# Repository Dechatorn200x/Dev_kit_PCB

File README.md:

# 🚀 PCB Design Skill Development & Integration Portfolio

คลังเก็บรวบรวมโปรเจกต์การออกแบบแผงวงจรพิมพ์ (PCB Design) 
วัตถุประสงค์หลักเพื่อการศึกษา, พัฒนาทักษะ และทดลองใช้งานจริงในระบบฮาร์ดแวร์ โดยมุ่งเน้นการประยุกต์ใช้งานด้านอิเล็กทรอนิกส์กำลัง (Power Electronics), ระบบควบคุมอุตสาหกรรม (Industrial Automation) และการจัดการสัญญาณสัญญาณรบกวน (Signal Integrity) ผ่านโปรแกรม **KiCad**

---

## 🎯 เป้าหมายการพัฒนาทักษะ (Skill Development Goals)

* **Hardware Topology Learning:** ศึกษาและฝึกฝนการออกแบบวงจรลดแรงดันประสิทธิภาพสูง (Buck Converter), วงจรคัดแยกสัญญาณแบบ Optocoupler และโครงสร้างพอร์ตสื่อสารต่างๆ
* **PCB Layout Best Practices:** พัฒนาทักษะการจัดวางชิ้นส่วนอุปกรณ์ (Component Placement), การเดินลายเส้นทองแดงตามข้อกำหนดขนาดกระแสไฟฟ้า (Trace Width Constraints) และการจัดการระนาบกราวด์ (Ground Plane Area)
* **Design for Manufacturing (DFM):** ฝึกฝนการนำข้อมูลลายวงจรออกในรูปแบบเอกสารการผลิตจริง เช่น ไฟล์ Gerber, Drill files และตาราง BOM (Bill of Materials) เพื่อใช้เตรียมส่งโรงงานผลิต

---

## 📂 รายการโปรเจกต์บอร์ดทดสอบในคลัง (Project Sub-folders)

ตัวคลังแบ่งสัดส่วนโครงการออกเป็นโฟลเดอร์ย่อยตามฟังก์ชันและชิปประมวลผลหลัก เพื่อป้องกันความสับสนในการจัดการเวอร์ชัน:

### 📦 [01] Arduino Nano Integration Kit (`/01_Nano_Kit`)
บอร์ดทดสอบอเนกประสงค์เพื่อฝึกทักษะการวางระบบอินเตอร์เฟสพื้นฐานเข้ากับไมโครคอนโทรลเลอร์ **Arduino Nano**
* **ฟังก์ชันการเรียนรู้:** * ออกแบบระบบ Buck Converter (LM2596) แปลงระดับแรงดัน 12V เป็น 5V 
  * ออกแบบชุดพอร์ตสื่อสาร I2C และวงจร USB to TTL เพิ่มเติมสำหรับงาน Debug
  * ออกแบบบล็อก GPIO Isolated ขับโหลดมอเตอร์กระแสตรง 12V แยกกราวด์ป้องกันสัญญาณรบกวนย้อนกลับด้วย Optocoupler
  * ฝึกทักษะการสลับช่องสัญญาณ (Mode Selection Jumper) ยืดหยุ่นทิศทางสัญญาณพอร์ต I2C วิ่งกลับไปพอร์ตอะนาล็อกและดิจิทัลของบอร์ดควบคุม

### 📦 [02] Future Projects... (`/02_...`)
*(Please follow me.)*

---

## 🛠️ โปรแกรมและเครื่องมือหลักที่ใช้งาน (Toolchain)

* **EDA Software:** KiCad Suite (เวอร์ชัน 9.0 หรือล่าสุด) สำหรับวาดผัง Schematic วาดลายเส้น PCB ลายทองแดง และจำลองโมเดลชิ้นส่วนแบบ 3 มิติ
* **Version Control:** Git & GitHub สำหรับเก็บบันทึกประวัติเวอร์ชันของบอร์ด และจัดการไฟล์แบ็กอัปขยะอย่างเป็นระบบด้วย `.gitignore`

---

## 📝 บันทึกความก้าวหน้าและการพัฒนา (Development Log)
* **[2026-06]:** จัดโครงสร้างคลังเก็บงานใหม่เข้าสู่ระบบ Sub-folders, ออกแบบและทดสอบผังวงจร Schematic ของบอร์ดทดลองแรก (Arduino Nano Integration Kit) สำเร็จลุล่วงเป็นระบบเปิด

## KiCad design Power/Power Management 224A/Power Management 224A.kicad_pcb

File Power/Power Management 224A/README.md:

# ⚡ Power Supply USB 5V-28V (Model: 224A)

โปรเจกต์บอร์ดจ่ายไฟอเนกประสงค์ควบคุมด้วยไอซี (IC-Based Adjustable Power Supply) รองรับการอินพุตพลังงานผ่านพอร์ต USB และสามารถปรับแรงดันเอาต์พุตได้ยืดหยุ่นตั้งแต่ **5V ถึง 28V** ออกแบบด้วยโปรแกรม KiCad เหมาะสำหรับนำไปใช้เป็นชุดทดสอบวงจร (Development Kit) บอร์ดขยายกำลัง หรือระบบจัดการพลังงานในงานอิเล็กทรอนิกส์

---

## 🛠️ คุณสมบัติทางเทคนิค (Features)
* **Input Voltage:** รองรับการจ่ายไฟเข้าผ่านพอร์ต USB (`V_USB`) และพอร์ต Screw Terminal
* **Output Voltage Range:** สามารถปรับแรงดันเอาต์พุตได้กว้างตั้งแต่ **5V ถึง 28V**
* **Safety & Protections:** * มีระบบป้องกันสัญญาณรบกวนและการไหลย้อนกลับของกระแสไฟฟ้า
  * ไฟแสดงสถานะความผิดพลาด (Error LED) สำหรับแจ้งเตือนระบบ
* **PCB Design:** ออกแบบบอร์ดแบบ 4 เลเยอร์ (4 layers Copper) พร้อมการจัดสัดส่วนลายทองแดงสำหรับไลน์กำลัง (Power Plane) และกราวด์ (GND Plane) ที่หนาแน่น

---

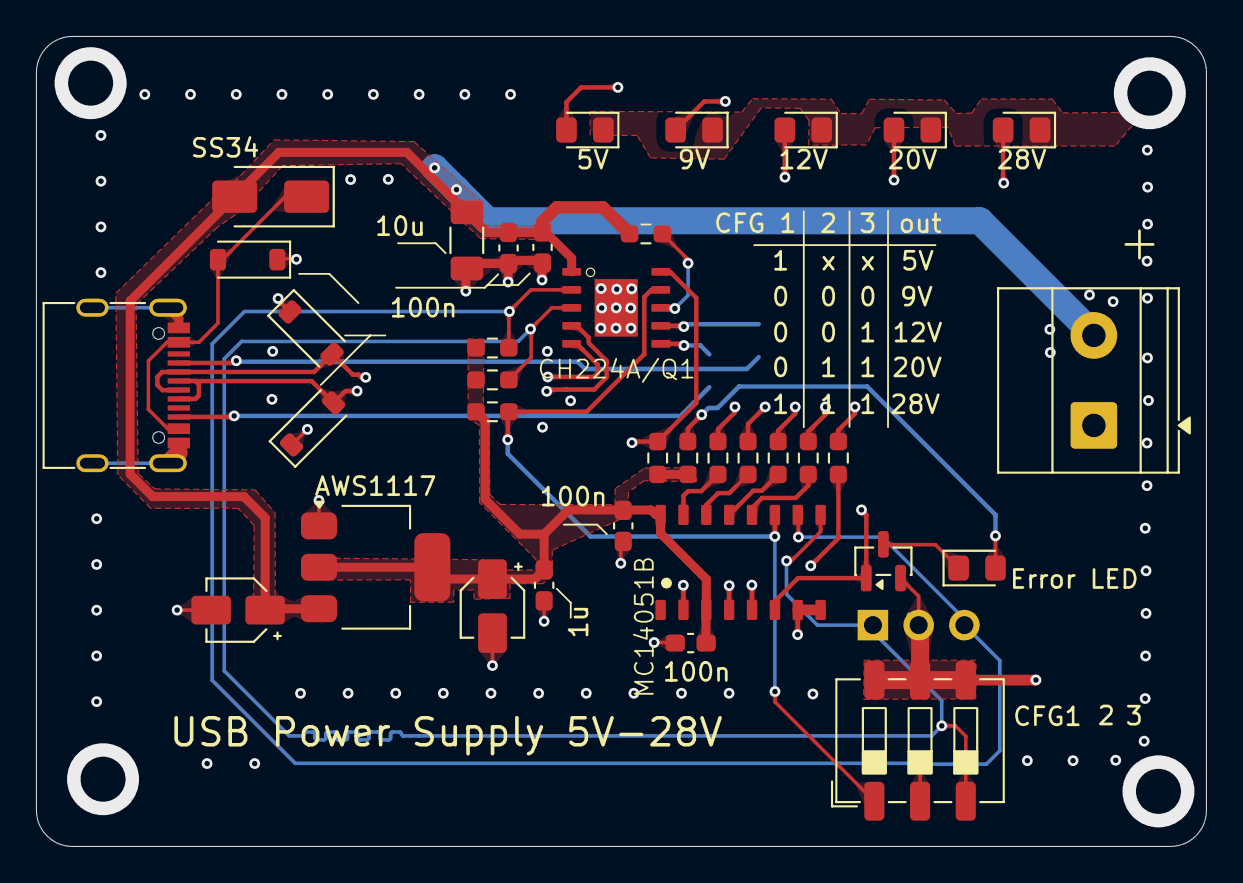
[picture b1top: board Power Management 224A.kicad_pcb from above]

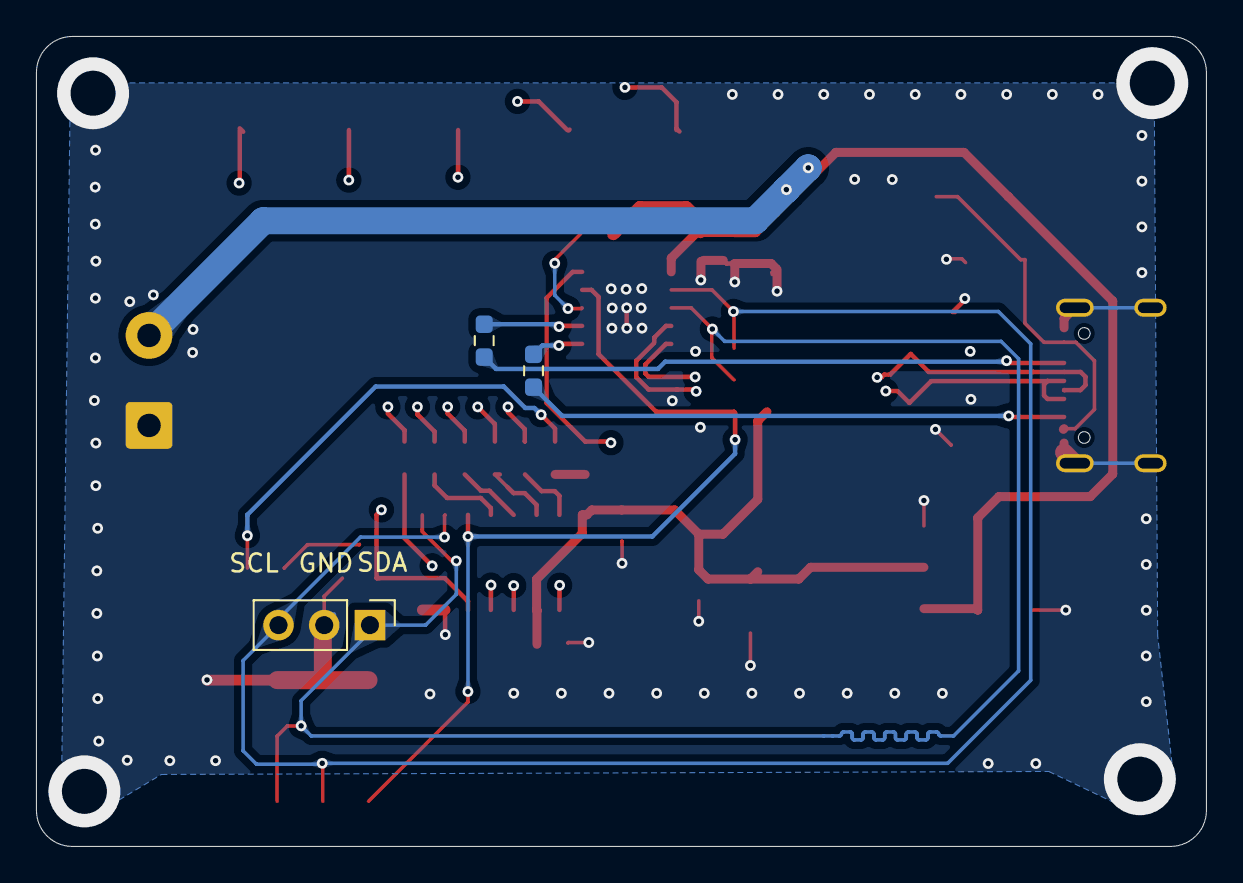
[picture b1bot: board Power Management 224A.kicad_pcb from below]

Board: 4 copper layers, 65.0 x 45.0 mm, 39 parts (3 on the bottom side), 27 nets.

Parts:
1K: 1k; R_0603_1608Metric_Pad0.98x0.95mm_HandSolder
1u: 1u; C_0603_1608Metric_Pad1.08x0.95mm_HandSolder
2N7002: 2N7002; SOT-23
5V, 9V, 12V, 20V, 28V: LED; LED_0805_2012Metric_Pad1.15x1.40mm_HandSolder
10k, 10k#2: 10k; R_0603_1608Metric_Pad0.98x0.95mm_HandSolder
100k: 100k; R_0603_1608Metric_Pad0.98x0.95mm_HandSolder
100n: 100n; C_0603_1608Metric_Pad1.08x0.95mm_HandSolder
+: Screw_Terminal_01x02; TerminalBlock_Phoenix_MKDS-1,5-2_1x02_P5.00mm_Horizontal
AWS1117: AMS1117-3.3; SOT-223-3_TabPin2
C1: 10u; C_1206_3216Metric_Pad1.33x1.80mm_HandSolder
C2, C3, C8: 100n; C_0603_1608Metric_Pad1.08x0.95mm_HandSolder
C5, C6: 10u; CP_Elec_3x5.4
CFG1: SW_DIP_x03; SW_DIP_SPSTx03_Slide_6.7x9.18mm_W6.73mm_P2.54mm_LowProfile_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
CH224A/Q1: ESSOP-10 224A
D2, D5: SMAJ5.0CA; D_SOD-123
D3: LED; LED_0805_2012Metric_Pad1.15x1.40mm_HandSolder
J1: USB_C_Receptacle_USB2.0_16P; USB_C_Receptacle_G-Switch_GT-USB-7010ASV
MC14051B: SOIC-MC1405B
R3, R4: 10k; R_0603_1608Metric_Pad0.98x0.95mm_HandSolder
R6, R7: 10; R_0603_1608Metric_Pad0.98x0.95mm_HandSolder
R8, R9, R10, R11, R13: 1k; R_0603_1608Metric_Pad0.98x0.95mm_HandSolder
SDA: Conn_01x03; PinHeader_1x03_P2.54mm_Vertical
SMAJ: SMAJ5.0CA; D_SOD-123
SS34: SS34; D_SMA

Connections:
+3.3V: 1u.1, 10k.1, 10k#2.1, 100n.1, AWS1117.2 (VO), C6.1, C8.1, MC14051B.3 (X), MC14051B.16 (VDD), R3.1, R4.1, R13.1
/CC1: CH224A/Q1.7 (CC1), R6.2
/CC2: CH224A/Q1.6 (CC2), R7.2
/CFG1: CFG1.1, CH224A/Q1.9 (CFG1), MC14051B.11 (A), R3.2
/CFG3/ SDA: CFG1.3, CH224A/Q1.3 (CGF3/_SDA), MC14051B.9 (C), R4.2, SDA.1
/CGF2/ SCL: 10k#2.2, CFG1.2, CH224A/Q1.2 (CGF2/_SCL), MC14051B.10 (B), SDA.3
/PG: 2N7002.1 (G), 10k.2, CH224A/Q1.10 (PG), MC14051B.6 (INH)
/USB_N: CH224A/Q1.5 (DM), J1.A7 (D-), J1.B7 (D-), SMAJ.2 (A2)
/USB_P: CH224A/Q1.4 (DP), D5.2 (A2), J1.A6 (D+), J1.B6 (D+)
/X0: MC14051B.13 (X0), R11.2
/X1: MC14051B.14 (X1), R10.2
/X2: MC14051B.15 (X2), R9.2
/X3: MC14051B.12 (X3), R8.2
/X4: 1K.2, MC14051B.2 (X6), MC14051B.4 (X7), MC14051B.5 (X5)
GND: 1u.2, 2N7002.2 (S), 5V.1 (K), 9V.1 (K), 12V.1 (K), 20V.1 (K), 28V.1 (K), 100n.2, +.1, AWS1117.1 (GND), C1.2, C2.2, C3.2, C5.2, C6.2, C8.2, CFG1.4, CFG1.5, CFG1.6, CH224A/Q1.0 (GND), D2.1 (A1), D5.1 (A1), J1.A1 (GND), J1.A12 (GND), J1.B1 (GND), J1.B12 (GND), J1.S1 (SHIELD), MC14051B.7 (VEE), MC14051B.8 (VSS), SDA.2, SMAJ.1 (A1)
unnamed: 100k.2, CH224A/Q1.8 (VBUS)
unnamed: D2.2 (A2), J1.A4 (VBUS), J1.A9 (VBUS), J1.B4 (VBUS), J1.B9 (VBUS), SS34.1 (K)
unnamed: D3.2 (A), R13.2
unnamed: 2N7002.3 (D), D3.1 (K)
unnamed: 1K.1, 5V.2 (A)
unnamed: 9V.2 (A), R11.1
unnamed: 12V.2 (A), R10.1
unnamed: 20V.2 (A), R9.1
unnamed: 28V.2 (A), R8.1
unnamed: J1.A5 (CC1), R6.1
unnamed: J1.B5 (CC2), R7.1
V_USB: 100k.1, +.2, AWS1117.3 (VI), C1.1, C2.1, C3.1, C5.1, CH224A/Q1.1 (VHV), SS34.2 (A)

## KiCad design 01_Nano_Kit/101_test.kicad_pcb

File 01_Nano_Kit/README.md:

# 🛠️ Arduino Nano Integration Kit Board

บอร์ดทดสอบอเนกประสงค์ (Development & Testing Board) สำหรับไมโครคอนโทรลเลอร์ Arduino Nano ที่ออกแบบมาเพื่อรองรับงานระบบควบคุมอุตสาหกรรม, การเชื่อมต่อโครงข่ายเซ็นเซอร์ และการขับโหลดกระแสสูงเบื้องต้น

---

## 📌 แนวคิดสำคัญในการออกแบบ (Design Concepts)

ตัวบอร์ดขับเคลื่อนด้วยสถาปัตยกรรมหลัก **MCU Arduino Nano** โดยรวบรวมบล็อกวงจรที่จำเป็นสำหรับงานอินเตอร์เฟสและควบคุมพื้นฐานไว้อย่างครบถ้วน:

1. **MCU Main Core:** รองรับโมดูลบอร์ดพัฒนา Arduino Nano ติดตั้งบนซ็อกเก็ตเพื่อความสะดวกในการซ่อมบำรุง
2. **Power Supply Stage:** วงจรลดแรงดันไฟเลี้ยงประสิทธิภาพสูงแบบ Buck Converter (LM2596) แปลงไฟเข้ากระแสตรง 12V เป็น 5V สำหรับเลี้ยงระบบหลัก
3. **Isolated Industrial Out (Drive Motor):** มีบล็อกวงจร GPIO OUT ขับโหลดไฟฟ้าแรงดัน 12V (ขับมอเตอร์/รีเลย์) แยกกราวด์ระบบด้วย Optocoupler ป้องกันสัญญาณรบกวนย้อนกลับทำลายชิปหลัก
4. **GPIO IN Stage:** วงจรอินพุตดิจิทัลรับสัญญาณจาก Switch พร้อมชุดตัวต้านทานและตัวเก็บประจุช่วยดักสัญญานป้องกันการเด้งของหน้าสัมผัส (Hardware Debounce)
5. **USB to TTL Interface:** ช่องสัญญาณพอร์ตสื่อสารซีเรียลเพิ่มเติมสำหรับการ Debug ข้อมูลผ่านคอมพิวเตอร์
6. **I2C Protocol Hub:** พอร์ตขยายสัญญาณสำหรับการเชื่อมต่อเซ็นเซอร์ความแม่นยำสูงภายนอก เช่น จอแสดงผล หรือโมดูลวัดค่าต่างๆ

---

## ⚙️ คุณสมบัติพิเศษด้านการสลับช่องสัญญาณ (Flexible Mode Selection)

เพื่อรองรับการพัฒนาระบบที่มีความยืดหยุ่นสูง บอร์ดนี้จึงได้รับการติดตั้ง **สวิตช์เลือกโหมดทำงาน (Mode Selection Jumper/Switch)** เพื่อจัดการทรัพยากรพอร์ต I2C ดังนี้:

* **I2C to Analog Pins Switching:** สามารถเปิดโหมดสลับสัญญานสายจากบล็อก I2C วิ่งตรงกลับมาเข้าพอร์ตอินพุตอะนาล็อก (Analog Pins) ของ Arduino Nano ได้ทุกช่องสัญญาณ
* **I2C to Digital Pins Switching:** สามารถเปลี่ยนโหมดกำหนดทิศทางสัญญาณ เพื่อวิ่งกลับเข้าใช้งานพอร์ตดิจิทัล (Digital Pins) ของ Arduino Nano ได้ทุกช่องสัญญาณตามความต้องการของซอฟต์แวร์

---

## 📊 ผังโครงสร้างลายวงจร (Schematic Preview)

---

## 📂 โครงสร้างไฟล์ในโปรเจกต์ (Project Structure)

* `101_test.kicad_pro` - ไฟล์หลักสำหรับเปิดโครงการในโปรแกรม KiCad 
* `101_test.kicad_sch` - แผนผังการเชื่อมต่อวงจรไฟฟ้าทั้งหมด (Schematic Diagram)
* `101_test.kicad_pcb` - ไฟล์การจัดวางชิ้นส่วนอุปกรณ์อิเล็กทรอนิกส์และการเดินลายทองแดง (PCB Layout)
* `.gitignore` - ไฟล์กำหนดขอบเขตสำหรับคัดกรองไม่ให้ส่งไฟล์แบ็กอัปขยะขึ้นสู่ระบบ Git Repository

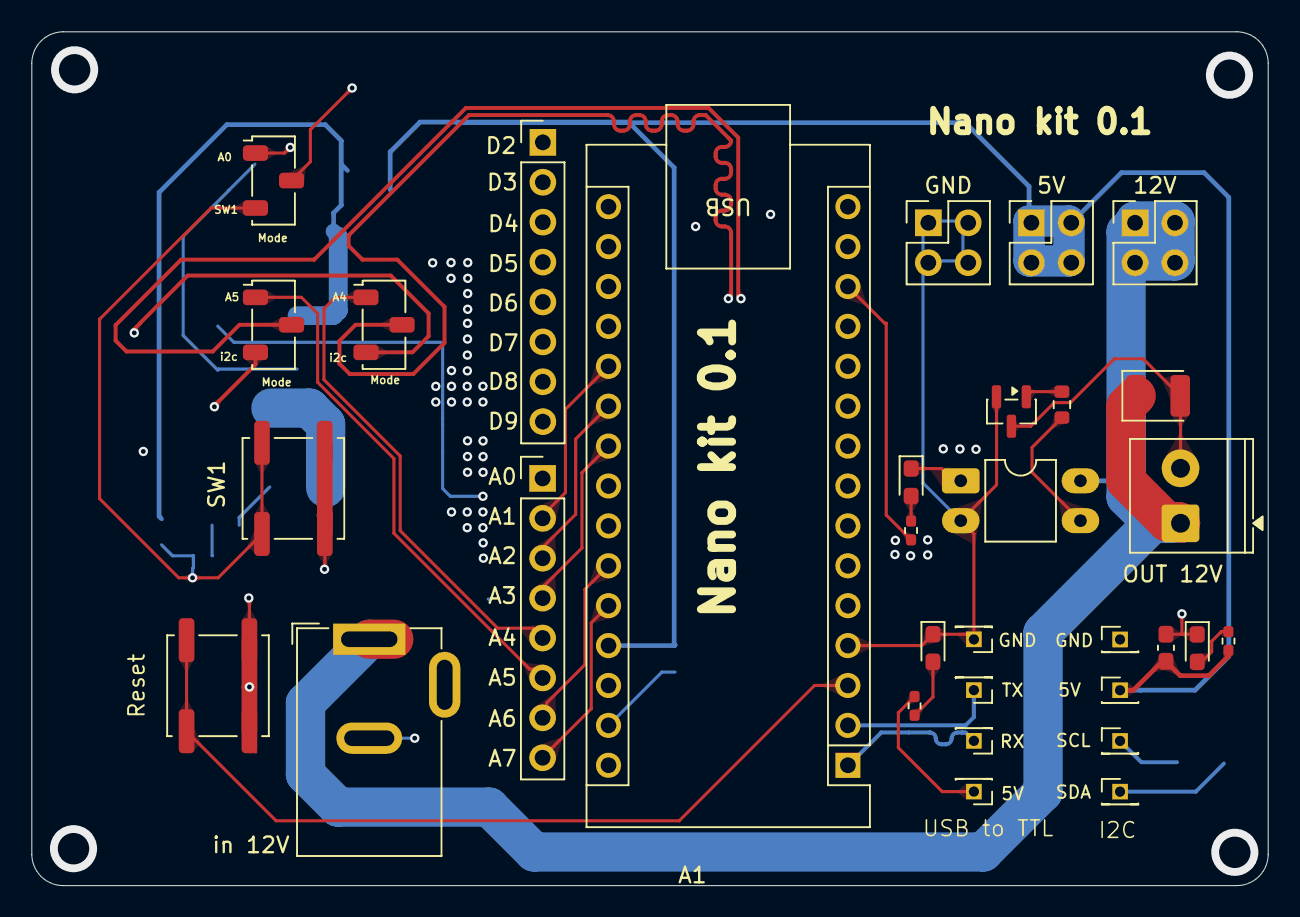
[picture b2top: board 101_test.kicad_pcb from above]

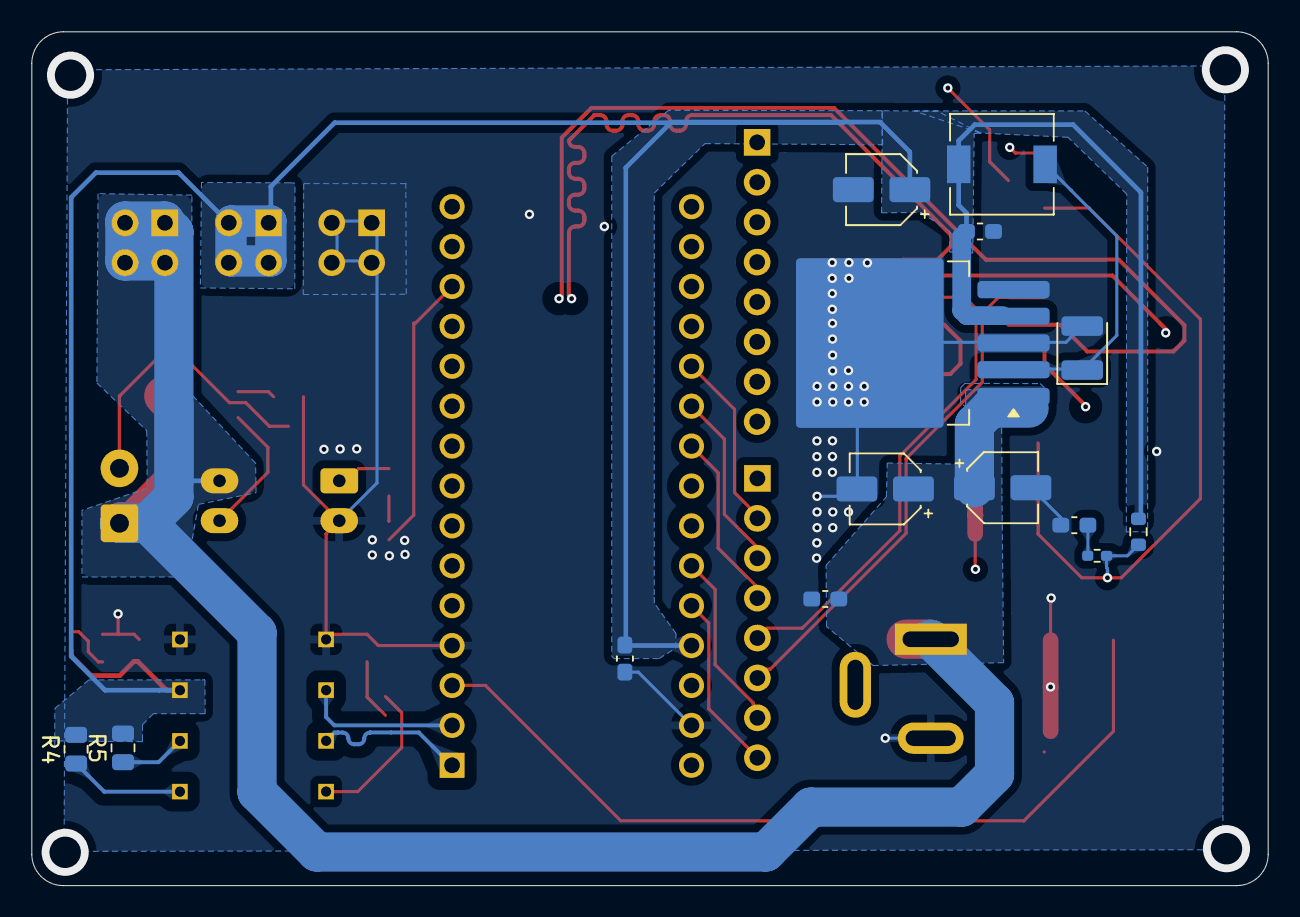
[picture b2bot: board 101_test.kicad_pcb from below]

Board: 4 copper layers, 78.7 x 54.4 mm, 46 parts (14 on the bottom side), 39 nets.

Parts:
5V: 5V; PinHeader_1x01_P1.27mm_Vertical
5V#2: 5V_com; PinHeader_1x01_P1.27mm_Vertical
5V#3, 12V: Conn_02x02_Counter_Clockwise; PinHeader_2x02_P2.54mm_Vertical
A1: Arduino_Nano_Every; Arduino_Nano
C1: 10u; CP_Elec_4x3.9
C2, C6: 1u; C_0603_1608Metric_Pad1.08x0.95mm_HandSolder
C3, C7, C8: 100n; C_0603_1608Metric_Pad1.08x0.95mm_HandSolder
C4: 680u; CP_Elec_4x3.9
C5: 220u; CP_Elec_4x3.9
D1: 1N5822; D_1210_3225Metric
D2: Conn_01x08; PinHeader_1x08_P2.54mm_Vertical
D2#2, D3, D4: LED; LED_0603_1608Metric_Pad1.05x0.95mm_HandSolder
D5: 1N4007; D_1210_3225Metric
GND: GND; PinHeader_1x01_P1.27mm_Vertical
GND#2: GND; PinHeader_1x01_P1.27mm_Vertical
GND#3: Conn_02x02_Counter_Clockwise; PinHeader_2x02_P2.54mm_Vertical
J14: Conn_01x08; PinHeader_1x08_P2.54mm_Vertical
L1: 33u; L_6.3x6.3_H3
OUT 12V: Relaypin; TerminalBlock_Phoenix_PT-1,5-2-3.5-H_1x02_P3.50mm_Horizontal
Q1: BC817; SOT-23
R1: 10K; R_0603_1608Metric
R2: 220; R_0402_1005Metric_Pad0.72x0.64mm_HandSolder
R3, R6, R7: 330; R_0402_1005Metric_Pad0.72x0.64mm_HandSolder
R4, R5: 4.7K; R_0805_2012Metric
R8: 1K; R_0603_1608Metric
RX: TX; PinHeader_1x01_P1.27mm_Vertical
Reset: SW_Push; SW_Push_1P1T_NO_CK_KSC6xxJ
SCL: SCL; PinHeader_1x01_P1.27mm_Vertical
SDA: SDA; PinHeader_1x01_P1.27mm_Vertical
SW1: SW_Push; SW_Push_1P1T_NO_CK_KSC6xxJ
SW3: A4 | SDA; Nidec_Copal_CAS-120A
SW4: A5 | SCL; Nidec_Copal_CAS-120A
SW5: A0 | GPIO IN; Nidec_Copal_CAS-120A
TX: RX; PinHeader_1x01_P1.27mm_Vertical
U1: LM2596S-5; TO-263-5_TabPin3
U2: OpTO817; DIP-4_W7.62mm_LongPads
in 12V: Jack-DC; BarrelJack_GCT_DCJ200-10-A_Horizontal

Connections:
+5V: 5V.1, 5V#3.1, 5V#3.2, 5V#3.3, 5V#3.4, A1.27 (+5V), C5.1, C6.2, C7.2, C8.2, L1.2, R1.1, R3.1, R4.2, R5.2, U1.4 (FB)
+12V: 12V.1, 12V.2, 12V.3, 12V.4, C1.1, C2.2, C4.1, D5.1 (K), OUT 12V.1, U1.1 (VIN), U2.4, in 12V.1
/i2c+: A1.23 (SDA/A4), SW3.2 (B)
/i2c-: A1.24 (SCL/A5), SW4.2 (B)
A0: D2.1, SW5.1 (C)
A1: A1.20 (A1), D2.2
A2: A1.21 (A2), D2.3
A3: A1.22 (A3), D2.4
A4: D2.5, SW3.1 (C)
A5: D2.6, SW4.1 (C)
A6: A1.25 (A6), D2.7
A7: A1.26 (A7), D2.8
D2: A1.5 (D2), J14.1
D3: A1.6 (D3), J14.2
D4: A1.7 (D4), J14.3
D5: A1.8 (D5), J14.4
D6: A1.9 (D6), J14.5
D7: A1.10 (D7), J14.6
D8: A1.11 (D8), J14.7
D9: A1.12 (D9), J14.8
GND: A1.4 (GND), A1.29 (GND), C1.2, C2.1, C3.2, C4.2, C5.2, C6.1, C7.1, C8.1, D1.2 (A), D2#2.1 (K), D4.1 (K), GND.1, GND#2.1, GND#3.1, GND#3.2, GND#3.3, GND#3.4, Q1.2 (E), Reset.1, SW1.1, U1.3 (GND), U1.5 (~ON/OFF), U2.2, in 12V.2
GPIO_OUT: A1.13 (D10), R6.1
I2C_+: R4.1, SDA.1, SW3.3 (A)
I2C_-: R5.1, SCL.1, SW4.3 (A)
unnamed: A1.19 (A0), SW5.2 (B)
unnamed: A1.3 (~RESET), Reset.2
unnamed: C3.1, R2.2
unnamed: D1.1 (K), L1.1, U1.2 (OUT)
unnamed: D2#2.2 (A), R3.2
unnamed: D3.2 (A), R6.2
unnamed: D3.1 (K), U2.1
unnamed: D4.2 (A), R7.2
unnamed: D5.2 (A), OUT 12V.2, Q1.3 (C)
unnamed: 5V#2.1, R7.1
unnamed: Q1.1 (B), R8.2
unnamed: R8.1, U2.3
SW1: R1.2, R2.1, SW1.2, SW5.3 (A)
UART_+: A1.1 (TX1), RX.1
UART_-: A1.2 (RX1), TX.1

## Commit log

2026-06-17 Structure: Initial multi-project repository with 01_Nano_Kit
2026-06-17 Manage folder && Docs: Update main repository README with skill development goals
2026-06-20 Update PCB layout: Add copper zone and fix DRC warning
2026-06-21 New USB-Power 5V-28V
2026-06-21 Clean up project: Add .gitignore and remove backup files
2026-06-21 Update README.md powersuppy
2026-06-21 add Schematic Power Supply
2026-06-26 Update Viapad
2026-06-26 Update Picture
